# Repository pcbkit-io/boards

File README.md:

# PCBKit boards

Circuit boards as plain KiCad projects, each one you can open in [PCBKit](https://pcbkit.io),
run as the device it is, and order. The KiCad files are the design; a board with a processor carries its program beside it
(`firmware/`, or the folder its `.pcbkit/device.yaml` names) and PCBKit builds it and runs the
image on its models of the board's chips, wired as the board's copper wires them: the same image
you flash onto the ordered board.

What a board cannot say itself is in its `.pcbkit/device.yaml`: the program's folder where it is
not `firmware`, files the program is built with and the repository does not hold (the Doom
boards' `DOOM1.WAD`, by address and SHA-256), a bare panel's size, the keys that work its
buttons. `pcbkit device plan` in a board's folder says what was recognised and how it is wired;
`pcbkit device build` and `pcbkit device run --seconds 5` build and run it.

| Folder | What is in it |
|---|---|
| [`devices/`](devices) | Real devices end to end: an STM32G431 sensor node on a robot's CAN bus and a 24 V AC thermostat on an ESP32, each with the world around it simulated |
| [`lab/`](lab) | Interactive boards: an ATmega328P (or two) running real C firmware against sensors, buttons, knobs, displays and servos you can change while it runs |
| [`arduino/`](arduino) | Arduino projects to play with: an Arduino Nano running a sketch with the usual libraries (Adafruit SSD1306 and SHT31, Sensirion SCD4x, LiquidCrystal, Servo): a weather station, a CO₂ monitor, a thermostat, a character-LCD runner, a pocket console with six games, Simon, a drawing screen |
| [`examples/`](examples) | Boards to learn from: a design PCBKit placed and routed from parts and connections, circuit blocks, open boards by their authors |
| [`assets/`](assets) | Files the simulation needs besides the boards: the boot ROMs of Espressif chips (Apache 2.0, from Espressif) |
| [`doom/`](doom) | Doom handhelds: eleven boards from a 10-cent CH32V003 to a Teensy 4.1 (RP2040, RP2350, ESP32-C3, ESP32-S3, STM32F411, i.MX RT1062), each ordered at JLCPCB as it is, flashed over USB and playing Doom from two 18650 cells |

Each folder is a family of boards with its own README; each board's folder is one project with
its README (what it is, how to order, flash and charge it, its parts and check results).

## The registry

[`registry.json`](registry.json) is the catalogue of these boards: their categories and, for each
board, its title, summary, tags, chips, licence, author, origin, folder, how it opens and whether
it is ready to order (`production`), as the schema [`registry.schema.json`](registry.schema.json)
says. PCBKit's app, its board library and pcbkit.io read nothing else: `node scripts/publish.mjs`
checks every board with the pcbkit command-line tool and publishes the registry and each board's
files to https://library.pcbkit.io/demos/ (the app reads it there without being rebuilt); a
board's picture is PCBKit's, drawn from its folder at the published commit
(`https://app.pcbkit.io/embed/github/pcbkit-io/boards/tree/<commit>/<path>.webp`). A new board: its
folder and an entry, then publish.

**Every interactive board is a real board**: it runs in the app, and it can be ordered from a
fab as it is and flashed after assembly (a USB bootloader or a programming header), so the image
that runs in the app runs on the board.

## Checking a board

`pcbkit check` in a board's folder runs KiCad's own electrical and design rule checks on it and
says what they found (the command comes with [PCBKit's plugin](https://github.com/pcbkit-io/agent-plugin)).

## Licences

Each family has its own: `devices/`, `lab/`, `arduino/` and `examples/` are CC0 1.0 (public domain), but for the open
boards by other authors, which keep theirs (`LICENSE.md` in their folders); `doom/` is the GNU GPL
v2 ([`doom/LICENSE`](doom/LICENSE)), the licence of the Doom engines it carries.

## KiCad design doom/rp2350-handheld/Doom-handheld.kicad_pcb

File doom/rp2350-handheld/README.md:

# RP2350 Doom handheld

A carrier board for a **Pimoroni Pico Plus 2** (RP2350B with 16 MB of flash and 8 MB of PSRAM)
under a **2.8" ILI9341 SPI TFT module** (the MSP2807, with touch), with a d-pad, strafe, fire, use,
menu and enter buttons. Power and flashing go through the Pico's USB-C. The outline is a red
keycard with a lanyard slot; the wordmark on the silkscreen is our own drawing.

## Run it in the browser

Open https://app.pcbkit.io/github/pcbkit-io/boards/tree/main/doom/rp2350-handheld, open
the Laboratory and press **Run**: the page builds `doom/` for the RP2350 (with `DOOM1.WAD` linked
into flash), boots the image on a register-level model of the chip and its PSRAM, and draws the
ILI9341's frames on the board. Play with the keyboard (arrows, F fire, Space use, comma/period
strafe, M menu, Enter) or a gamepad (`input.js` maps a standard controller).

## Parts

| Ref | Part | Note |
|---|---|---|
| U1 | Pimoroni Pico Plus 2 (PIM722) | on the back, on two 1x20 headers |
| lcd | 2.8" ILI9341 SPI TFT with touch (MSP2807) | on a 1x14 female header; the touch shares SPI0 and stays deselected |
| up, down, left, right, strafeLeft, strafeRight, fire, use, menu, enter | 6 x 6 mm tactile switch | to ground; the RP2350's pull-ups |
| J1 | 1x3 2.54 mm header | the console: UART0 at 115200 baud (TX, RX, GND) |
| BT1, BT2, F1, F2 | two Keystone 1042 18650 holders on the back; 2 A resettable fuses (Littelfuse 1812L200/16GR) | the cells in parallel, each through its own fuse (a cell put in backwards trips them instead of shorting the other), then the reverse-cell P-FET and DW01A + FS8205A protection |

## Pins

| Signal | GPIO |
|---|---|
| Display SCK, MOSI (SPI0) | GP18, GP19 |
| Display CS, D/C, RESET, backlight | GP17, GP20, GP21, GP22 |
| Up, down, left, right, fire, use, strafe left, strafe right, menu, enter | GP2 … GP11 |
| Console TX, RX (UART0) | GP0, GP1 |
| PSRAM chip select | GP47 (on the Pico Plus 2) |

## The firmware

`doom/doom_rp2350.c` is the platform layer: clocks (12 MHz crystal, 150 MHz from the PLL), the
PSRAM on the QSPI interface, the display over SPI0 at 25 MHz, the buttons, the timer. The engine
in `doom/` is sysprog21/doom_riscv, unchanged. The program runs on the RP2350's RISC-V (Hazard3)
cores from flash; the zone heap and the screens are in PSRAM. There is no sound.

The simulation runs one instruction per clock and does not charge flash or PSRAM latency, so the
board itself may draw fewer frames per second than the browser shows.

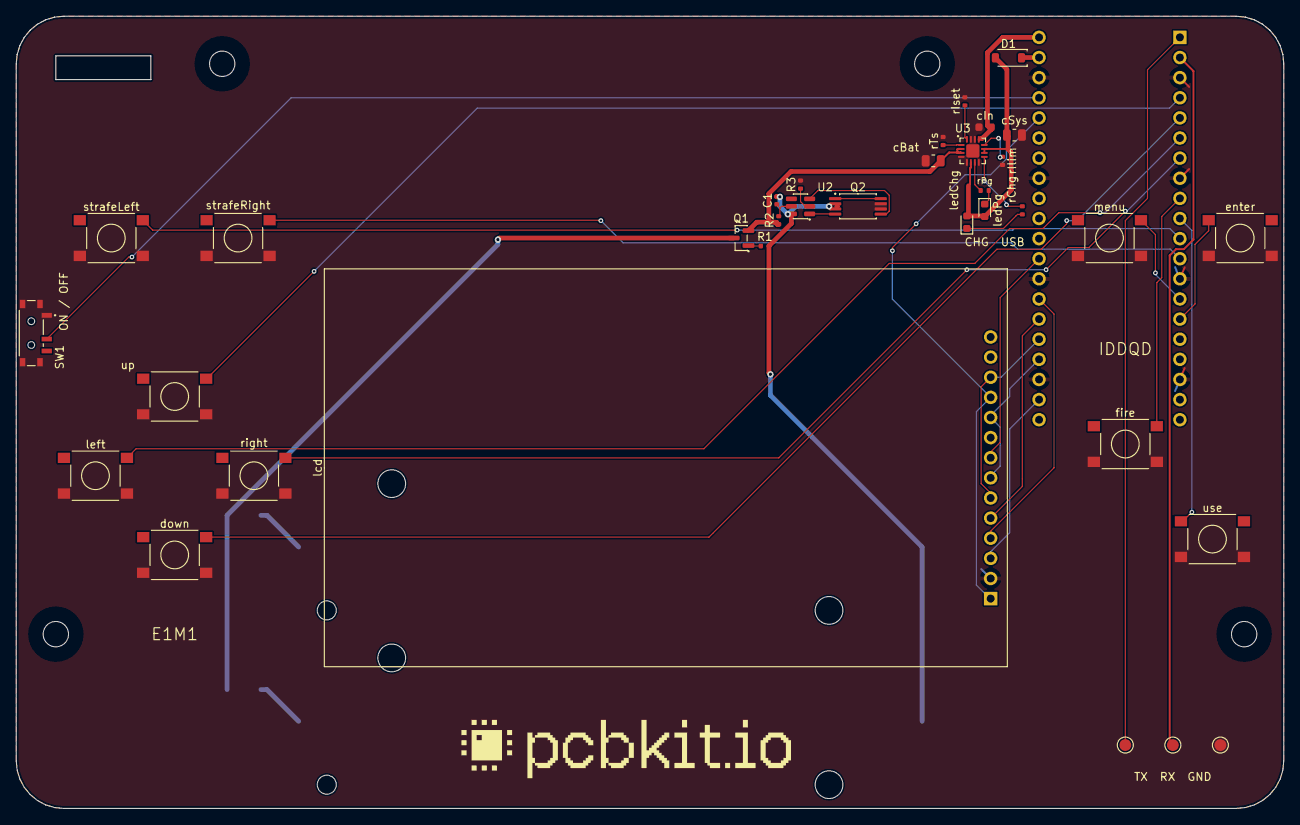
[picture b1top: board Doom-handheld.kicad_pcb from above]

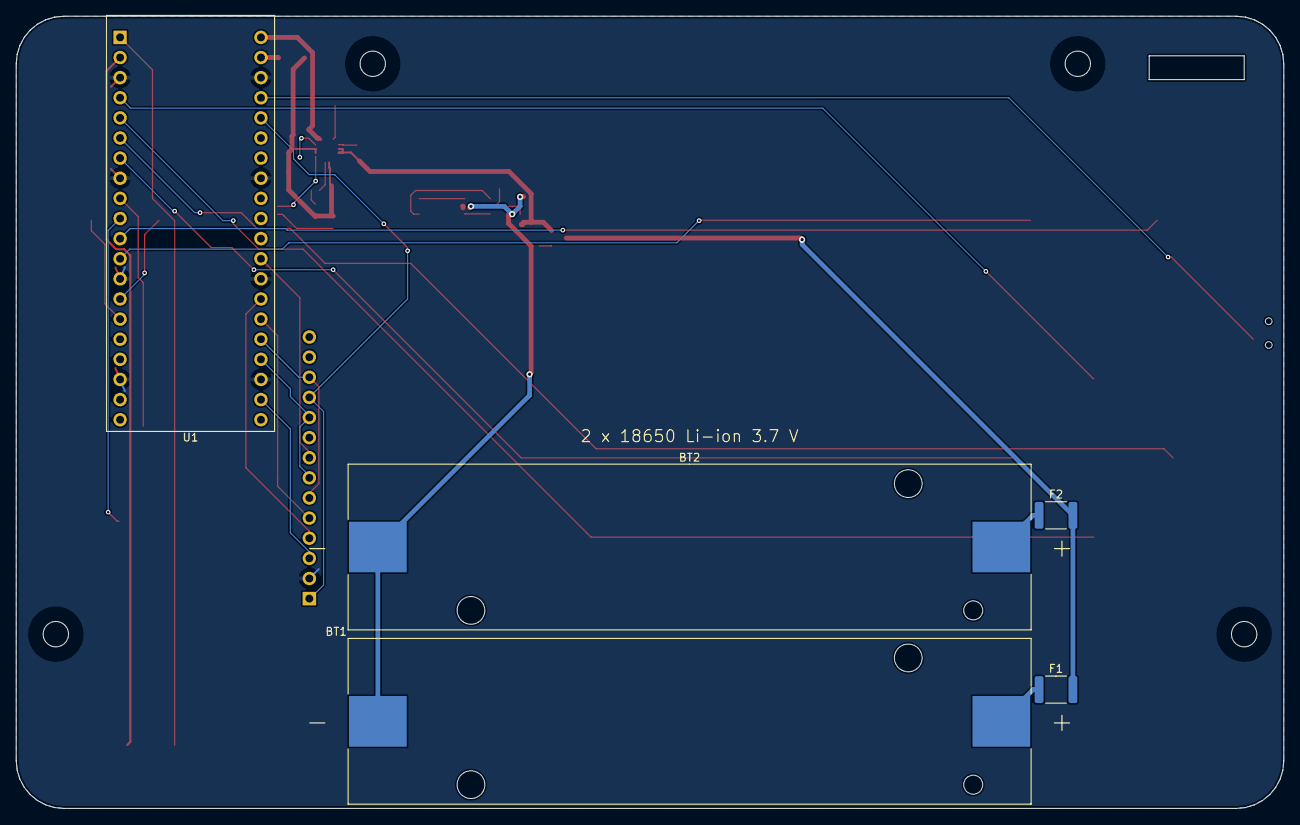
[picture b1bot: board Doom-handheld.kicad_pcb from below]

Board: 2 copper layers, 160.0 x 100.0 mm, 44 parts (5 on the bottom side), 42 nets.

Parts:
BT1, BT2: 1042; BatteryHolder_Keystone_1042_1x18650
C1: 100nF; C_0402_1005Metric
D1: 1N5819HW-7-F; D_SOD-123
F1, F2: PTC 2000mA; Fuse_1812_4532Metric
H1, H2, H3, H4: MountingHole_3.2mm_M3
Q1: AO3401A; SOT-23
Q2: FS8205A; TSSOP-8_4.4x2.93mm_P0.65mm
R1: 100kohm; R_0402_1005Metric
R2: 100ohm; R_0402_1005Metric
R3: 1kohm; R_0402_1005Metric
SW1: MSK12C02; SW_Slide_SPDT_Shouhan_MSK12C02
U1: PIM724; Pimoroni_Pico_Plus_2_Socket_2x20_P2.54mm_W17.78mm
U2: DW01A; SOT-6_1.6x2.9mm_P0.95mm
U3: BQ24075RGTR; QFN-16-1EP_3x3mm_P0.5mm_EP1.68x1.68mm
cBat: 4.7uF; C_0805_2012Metric
cIn: 1uF; C_0603_1608Metric
cSys: 4.7uF; C_0805_2012Metric
down: PTS645SM43SMTR92 LFS; SW_Tactile_SPST_6x6mm_SMD
enter: PTS645SM43SMTR92 LFS; SW_Tactile_SPST_6x6mm_SMD
fire: PTS645SM43SMTR92 LFS; SW_Tactile_SPST_6x6mm_SMD
lcd: MSP2807 2.8in 240x320 SPI TFT module with touch (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; TFT_2.8in_ILI9341_Socket_1x14_P2.54mm
ledChg: red; LED_0603_1608Metric
ledPg: green; LED_0603_1608Metric
left: PTS645SM43SMTR92 LFS; SW_Tactile_SPST_6x6mm_SMD
logo: Logo_PCBKit_pcbkit.io
menu: PTS645SM43SMTR92 LFS; SW_Tactile_SPST_6x6mm_SMD
rChg: 1.5kohm; R_0402_1005Metric
rIlim: 1.18kohm; R_0402_1005Metric
rIset: 1.13kohm; R_0402_1005Metric
rPg: 1.5kohm; R_0402_1005Metric
rTs: 10kohm; R_0402_1005Metric
right: PTS645SM43SMTR92 LFS; SW_Tactile_SPST_6x6mm_SMD
strafeLeft: PTS645SM43SMTR92 LFS; SW_Tactile_SPST_6x6mm_SMD
strafeRight: PTS645SM43SMTR92 LFS; SW_Tactile_SPST_6x6mm_SMD
tpGnd: TestPoint_Round_D1.5mm
tpRx: TestPoint_Round_D1.5mm
tpTx: TestPoint_Round_D1.5mm
up: PTS645SM43SMTR92 LFS; SW_Tactile_SPST_6x6mm_SMD
use: PTS645SM43SMTR92 LFS; SW_Tactile_SPST_6x6mm_SMD

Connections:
BAT: Q1.2 (S), R2.1 (a), U3.2 (BAT), U3.3 (BAT), cBat.1 (a)
BAT_IN: F1.2 (b), F2.2 (b), Q1.3 (D)
CELL1_P: BT1.2 (C2), F1.1 (a)
CELL2_P: BT2.2 (C2), F2.1 (a)
CELL_N: BT1.1 (C1), BT2.1 (C1), C1.2 (b), Q2.2 (S1), Q2.3 (S1), R1.2 (b), U2.6 (GND)
CHG_LED: ledChg.1 (K), rChg.1 (a)
CHG_N: U3.9 (nCHG), rChg.2 (b)
DOWN: U1.5 (GP3), down.1 (a)
ENTER: U1.15 (GP11), enter.1 (a)
FIRE: U1.9 (GP6), fire.1 (a)
GND: Q2.6 (S2), Q2.7 (S2), R3.2 (b), SW1.1 (A), SW1.4 (SHELL), U1.3 (GND), U1.8 (GND), U1.13 (GND), U1.18 (GND), U1.23 (GND), U1.28 (GND), U1.33 (AGND), U1.38 (GND), U3.4 (nCE), U3.5 (EN2), U3.8 (VSS), U3.14 (TMR), U3.15 (SYSOFF), U3.17 (VSS), cBat.2 (b), cIn.2 (b), cSys.2 (b), down.2 (b), enter.2 (b), fire.2 (b), lcd.2 (GND), left.2 (b), menu.2 (b), rIlim.2 (b), rIset.2 (b), rTs.2 (b), right.2 (b), strafeLeft.2 (b), strafeRight.2 (b), tpGnd.1, up.2 (b), use.2 (b)
ILIM: U3.12 (ILIM), rIlim.1 (a)
ISET: U3.16 (ISET), rIset.1 (a)
LCD_CS: U1.22 (GP17), lcd.3 (CS)
LCD_DC: U1.26 (GP20), lcd.5 (DC)
LCD_LED: U1.29 (GP22), lcd.8 (LED)
LCD_MOSI: U1.25 (GP19), lcd.6 (SDI), lcd.12 (T_DIN)
LCD_RESET: U1.27 (GP21), lcd.4 (RESET)
LCD_SCK: U1.24 (GP18), lcd.7 (SCK), lcd.10 (T_CLK)
LEFT: U1.6 (GP4), left.1 (a)
MENU: U1.14 (GP10), menu.1 (a)
unnamed: C1.1 (a), R2.2 (b), U2.5 (VCC)
unnamed: Q2.4 (G1), U2.1 (OD)
unnamed: Q2.5 (G2), U2.3 (OC)
unnamed: R3.1 (a), U2.2 (CS)
PG_LED: ledPg.1 (K), rPg.2 (b)
PG_N: U3.7 (nPGOOD), rPg.1 (a)
PWR_EN: SW1.2 (COM), U1.37 (P3V3_EN)
RIGHT: U1.7 (GP5), right.1 (a)
RX: U1.2 (GP1), tpRx.1
STRAFE_L: U1.11 (GP8), strafeLeft.1 (a)
STRAFE_R: U1.12 (GP9), strafeRight.1 (a)
SYS: D1.2 (A), U3.6 (EN1), U3.10 (OUT), U3.11 (OUT), cSys.1 (a), ledChg.2 (A), ledPg.2 (A)
TS: U3.1 (TS), rTs.1 (a)
TX: U1.1 (GP0), tpTx.1
U2Support/DRAIN: Q2.1 (D12), Q2.8 (D12)
UP: U1.4 (GP2), up.1 (a)
USE: U1.10 (GP7), use.1 (a)
V3: U1.36 (P3V3), lcd.1 (VCC), lcd.11 (T_CS)
VBUS: U1.40 (VBUS), U3.13 (IN), cIn.1 (a)
VSYS: D1.1 (K), U1.39 (VSYS)
reversed/gate: Q1.1 (G), R1.1 (a)

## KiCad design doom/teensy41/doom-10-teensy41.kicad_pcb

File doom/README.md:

# Doom handhelds

Circuit boards that run Doom, designed in [PCBKit](https://pcbkit.io). Every board is a PCBKit
project (a KiCad project with its `.pcbkit/` design): open one in the app, press **Run**, and the
same firmware that would be flashed onto the ordered board is built in your browser and plays
there on a simulation of its chips; order the board, flash the image, and it plays on the desk.

Open them at **https://app.pcbkit.io/github/pcbkit-io/boards/tree/main/doom**.

| Board | What it is |
|---|---|
| [`rp2350-handheld`](rp2350-handheld) | Pimoroni Pico Plus 2 (RP2350B, 16 MB flash, 8 MB PSRAM) under a 2.8" ILI9341 screen, ten buttons, USB-C power; a red keycard with a lanyard slot |

Ten more designs explore the range, from the cheapest chip that can run Doom at all to a
Cortex-M7 at 600 MHz: different processors, screens, memories and sound, one power design. Each
is routed, passes `check` and is ready to order, and each has its program in `doom/`: opened from
its GitHub link in PCBKit, it builds in the page and plays in the simulation, and its README says
how to flash it over USB on arrival.

| Board | Processor | Screen | Flashing on arrival |
|---|---|---|---|
| [`v003-emu`](v003-emu) | CH32V003 (RISC-V, 2 KB RAM) emulating a larger RISC-V, game in 8 MB SPI PSRAM | Nokia 5110 | WCH-LinkE on the SWIO header |
| [`pico-oled`](pico-oled) | Raspberry Pi Pico (RP2040) on sockets | 2.42" mono OLED | the Pico's USB: BOOTSEL, UF2 |
| [`c3-pocket`](c3-pocket) | ESP32-C3 module (RISC-V) | 1.3" colour TFT | USB-C: the C3's USB Serial/JTAG (esptool) |
| [`rp2040-tft`](rp2040-tft) | bare RP2040, 16 MB flash, microSD, PWM sound | 1.8" colour TFT | USB-C: BOOT + RESET, UF2; SWD header |
| [`f411-psram`](f411-psram) | STM32F411 (Cortex-M4F) with 8 MB SPI PSRAM and flash, I2S amplifier | 2.0" TFT | USB-C: the ROM's DFU (BOOT + RESET); SWD header |
| [`pico2-carrier`](pico2-carrier) | Pimoroni Pico Plus 2 carrier with a headphone DAC | 2.8" ILI9341 touch | the module's USB: BOOTSEL, UF2 |
| [`rp2350-psram`](rp2350-psram) | bare RP2350A with QSPI flash and 8 MB PSRAM, microSD, I2S amplifier, fuel gauge | 2.0" TFT | USB-C: BOOT + RESET, UF2; SWD header |
| [`s3-handheld`](s3-handheld) | ESP32-S3 module (Xtensa, 8 MB PSRAM), microSD, I2S amplifier, fuel gauge | 2.8" touch TFT | USB-C: the S3's USB Serial/JTAG (esptool) |
| [`s3-rgb`](s3-rgb) | ESP32-S3 driving a raw 480×272 RGB panel, buttons on an I2C expander, stereo DAC | 4.3" RGB | USB-C: the S3's USB Serial/JTAG (esptool) |
| [`teensy41`](teensy41) | Teensy 4.1 (Cortex-M7, 600 MHz), DAC with jack and speaker, fuel gauge | 3.5" touch TFT | the Teensy's USB: Teensy Loader |

Every board runs from **two 18650 Li-ion cells in parallel** (1S2P, Keystone 1042 holders on the
back) behind a reverse-cell P-MOSFET and DW01A + FS8205A protection, charged over USB by a BQ24075
with power path (the board runs from USB while it charges), as [`rp2350-handheld`](rp2350-handheld)
does. Every assembled part has an LCSC code for JLCPCB's assembly; modules and screens plug into
sockets it solders. Each board's README says how to charge it, how to flash it, what to plug in
by hand and its parts, with its `check` and readiness results.

## Licences

- The game engine in each board's `doom/` is id Software's Linux Doom source as released under the
  GNU GPL v2: [sysprog21/doom_riscv](https://github.com/sysprog21/doom_riscv) at `81ccabe`
  unchanged on most boards; [kilograham/rp2040-doom](https://github.com/kilograham/rp2040-doom) at
  `29a453c` (GPL v2, its compressed level format) on `pico-oled`, `rp2040-tft` and `c3-pocket`, with
  the changes PCBKit's kits need marked `PCBKIT`.
- Everything else here (the boards, their designs and KiCad files, the platform layers
  `doom/doom_*.c`, the simulations' scripts) is by PCBKit, under the same licence: the GNU
  General Public License v2 ([`LICENSE`](LICENSE)).
- The game's data is not in this repository. Each design declares the shareware `DOOM1.WAD` (or
  rp2040-doom's compressed `DOOM1.WHX`; id Software, free to share unmodified) by where it is
  published and its SHA-256; the build downloads it, checks it and links it into the firmware.

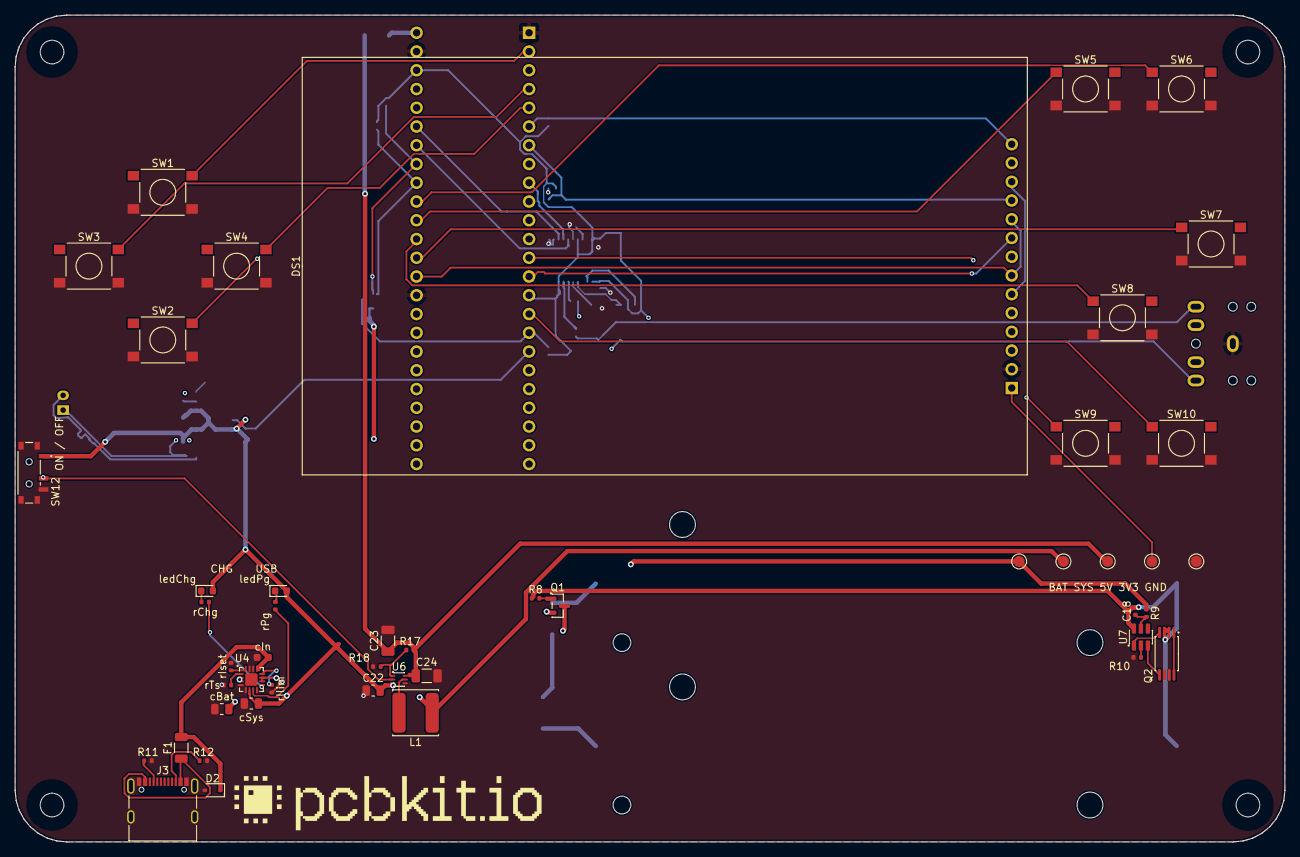
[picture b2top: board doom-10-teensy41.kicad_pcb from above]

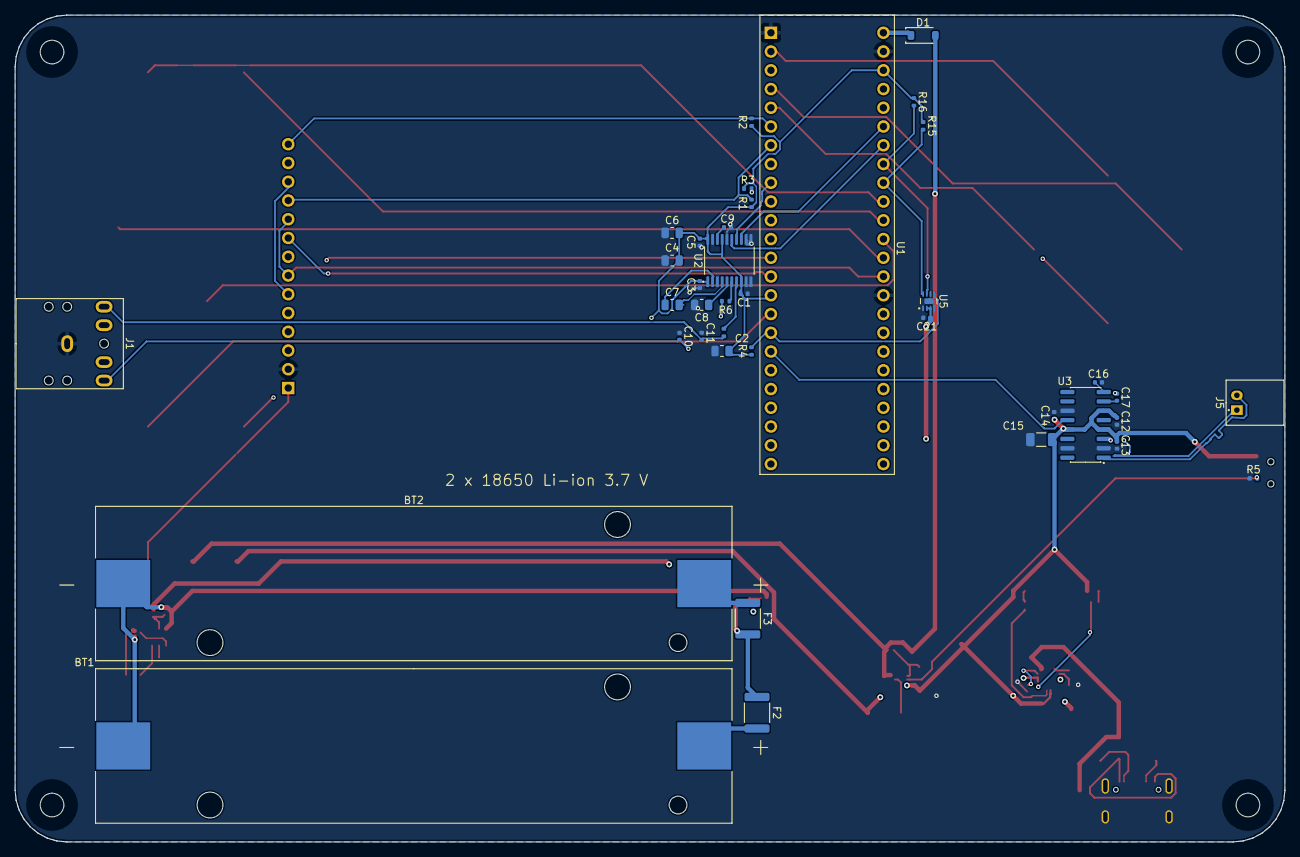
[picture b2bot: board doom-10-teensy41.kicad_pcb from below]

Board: 4 copper layers, 172.0 x 112.0 mm, 90 parts (38 on the bottom side), 68 nets.

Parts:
BT1, BT2: 1042; BatteryHolder_Keystone_1042_1x18650
C1, C3, C5, C9, C18, C21: 100nF; C_0402_1005Metric
C2, C4, C6, C22: 10uF; C_0805_2012Metric
C7, C8: 2.2uF; C_0805_2012Metric
C10, C11: 2.2nF; C_0402_1005Metric
C12, C13, C14, C16: 1uF; C_0402_1005Metric
C15, C23, C24: 22uF; C_1206_3216Metric
C17: 470nF; C_0402_1005Metric
D1: 1N5819HW-7-F; D_SOD-123
D2: tvs 5V; D_SOD-323
DS1: MSP3520 3.5in 320x480 SPI TFT module with touch (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; TFT_3.5in_ILI9488_Socket_1x14_P2.54mm
F1: PTC 1100mA; Fuse_1206_3216Metric
F2, F3: PTC 2000mA; Fuse_1812_4532Metric
H1, H2, H3, H4: MountingHole_3.2mm_M3
J1: SJ1-3525N; Jack_3.5mm_SameSky_SJ1-352XN_Horizontal
J3: USB4105-GF-A; USB_C_Receptacle_USB2.0_16P
J5: S2B-PH-K-S(LF)(SN); JST_PH_S2B-PH-K_1x02_P2.00mm_Horizontal
L1: 1uH; L_Power_6x6mm
Q1: AO3401A; SOT-23
Q2: FS8205A; TSSOP-8_4.4x2.93mm_P0.65mm
R1, R2, R3, R4: 10kohm; R_0402_1005Metric
R5: 1Mohm; R_0402_1005Metric
R6, R7: 470ohm; R_0402_1005Metric
R8, R18: 100kohm; R_0402_1005Metric
R9: 100ohm; R_0402_1005Metric
R10: 1kohm; R_0402_1005Metric
R11, R12: 5.1kohm; R_0402_1005Metric
R15, R16: 3.3kohm; R_0402_1005Metric
R17: 732kohm; R_0402_1005Metric
SW1, SW2, SW3, SW4, SW5, SW6, SW7, SW8, SW9, SW10: PTS645SM43SMTR92 LFS; SW_Tactile_SPST_6x6mm_SMD
SW12: MSK12C02; SW_Slide_SPDT_Shouhan_MSK12C02
U1: TEENSY41; Teensy41_Socket_2x24_P2.54mm_W15.24mm
U2: PCM5102APWR; TSSOP-20_4.4x6.5mm_P0.65mm
U3: PAM8403DR; SOIC-16_3.9x9.9mm_P1.27mm
U4: BQ24075RGTR; QFN-16-1EP_3x3mm_P0.5mm_EP1.68x1.68mm
U5: MAX17048G+T10; DFN-8-1EP_2x2mm_P0.5mm_EP0.8x1.2mm
U6: TPS61023DRLR; SOT-563
U7: DW01A; SOT-6_1.6x2.9mm_P0.95mm
cBat: 4.7uF; C_0805_2012Metric
cIn: 1uF; C_0603_1608Metric
cSys: 4.7uF; C_0805_2012Metric
ledChg: red; LED_0603_1608Metric
ledPg: green; LED_0603_1608Metric
logo: Logo_PCBKit_pcbkit.io
rChg: 1.5kohm; R_0402_1005Metric
rIlim: 1.18kohm; R_0402_1005Metric
rIset: 1.13kohm; R_0402_1005Metric
rPg: 1.5kohm; R_0402_1005Metric
rTs: 10kohm; R_0402_1005Metric
tpBat: TestPoint_Round_D1.5mm
tpGnd: TestPoint_Round_D1.5mm
tpSys: TestPoint_Round_D1.5mm
tpV3, tpV5: TestPoint_Round_D1.5mm

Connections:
AMP_SD: U1.18 (D26), U3.12 (SHDN)
BAT: C21.1 (a), Q1.2 (S), R9.1 (a), U4.2 (BAT), U4.3 (BAT), U5.2 (CELL), U5.3 (VDD), cBat.1 (a), tpBat.1
BAT_IN: F2.2 (b), F3.2 (b), Q1.3 (D)
BOOST_EN: R5.1 (a), SW12.2 (COM), U6.2 (EN)
CELL1_P: BT1.2 (C2), F2.1 (a)
CELL2_P: BT2.2 (C2), F3.1 (a)
CELL_N: BT1.1 (C1), BT2.1 (C1), C18.2 (b), Q2.2 (S1), Q2.3 (S1), R8.2 (b), U7.6 (GND)
CHG_LED: ledChg.1 (K), rChg.2 (b)
CHG_N: U4.9 (nCHG), rChg.1 (a)
DAC_LDO: C9.1 (a), U2.18 (LDOO)
DAC_VNEG: C8.1 (a), U2.5 (VNEG)
DOWN: SW2.1 (a), U1.3 (D1)
ENTER: SW10.1 (a), U1.16 (D24)
FIRE: SW7.1 (a), U1.37 (D14)
FUEL_ALRT: R4.2 (b), U1.17 (D25), U5.5 (ALRT)
GND: C1.2 (b), C2.2 (b), C3.2 (b), C4.2 (b), C5.2 (b), C6.2 (b), C8.2 (b), C9.2 (b), C10.2 (b), C11.2 (b), C12.2 (b), C13.2 (b), C14.2 (b), C15.2 (b), C16.2 (b), C21.2 (b), C22.2 (b), C23.2 (b), C24.2 (b), D2.2 (A), DS1.2 (GND), J1.1 (SLEEVE), J3.A1 (GND), J3.A12, J3.B1 (GND), J3.B12, J3.S1 (SHIELD), Q2.6 (S2), Q2.7 (S2), R5.2 (b), R10.2 (b), R11.2 (b), R12.2 (b), R18.2 (b), SW1.2 (b), SW2.2 (b), SW3.2 (b), SW4.2 (b), SW5.2 (b), SW6.2 (b), SW7.2 (b), SW8.2 (b), SW9.2 (b), SW10.2 (b), SW12.3 (B), SW12.4 (SHELL), U1.1 (GND), U1.26 (GND), U1.39 (GND), U2.3 (CPGND), U2.9 (AGND), U2.10 (DEMP), U2.11 (FLT), U2.12 (SCK), U2.16 (FMT), U2.19 (DGND), U3.2 (PGND), U3.11 (GND), U3.15 (PGND), U4.4 (nCE), U4.5 (EN2), U4.8 (VSS), U4.14 (TMR), U4.15 (SYSOFF), U4.17 (VSS), U5.1 (CTG), U5.4 (GND), U5.6 (QSTRT), U5.9 (EP), U6.4 (GND), cBat.2 (b), cIn.2 (b), cSys.2 (b), rIlim.2 (b), rIset.2 (b), rTs.2 (b), tpGnd.1
I2S_BCK: U1.30 (D21), U2.13 (BCK)
I2S_DIN: U1.9 (D7), U2.14 (DIN)
I2S_LRCK: U1.31 (D20), U2.15 (LRCK)
ILIM: U4.12 (ILIM), rIlim.1 (a)
ISET: U4.16 (ISET), rIset.1 (a)
LCD_BL: DS1.8 (LED), U1.8 (D6)
LCD_CS: DS1.3 (CS), R3.2 (b), U1.12 (D10)
LCD_DC: DS1.5 (DC), U1.11 (D9)
LCD_RST: DS1.4 (RESET), U1.10 (D8)
LEFT: SW3.1 (a), U1.4 (D2)
LINE_L: C10.1 (a), C17.1 (a), J1.2 (TIP), R6.2 (b)
LINE_R: C11.1 (a), J1.3 (RING), R7.1 (a)
MENU: SW9.1 (a), U1.29 (D22)
MISO: DS1.9 (SDO), DS1.13 (T_DO), U1.14 (D12)
MOSI: DS1.6 (SDI), DS1.12 (T_DIN), U1.13 (D11)
unnamed: C7.2 (b), U2.2 (CAPP)
unnamed: C7.1 (a), U2.4 (CAPM)
unnamed: C16.1 (a), U3.8 (VREF)
unnamed: C17.2 (b), U3.7 (INL)
unnamed: C18.1 (a), R9.2 (b), U7.5 (VCC)
unnamed: L1.2 (b), U6.5 (SW)
unnamed: Q2.4 (G1), U7.1 (OD)
unnamed: Q2.5 (G2), U7.3 (OC)
unnamed: R6.1 (a), U2.6 (OUTL)
unnamed: R7.2 (b), U2.7 (OUTR)
unnamed: R10.1 (a), U7.2 (CS)
unnamed: R17.1 (a), R18.1 (a), U6.1 (FB)
PG_LED: ledPg.1 (K), rPg.1 (a)
PG_N: U4.7 (nPGOOD), rPg.2 (b)
RIGHT: SW4.1 (a), U1.5 (D3)
SCK: DS1.7 (SCK), DS1.10 (T_CLK), U1.38 (D13)
SCL: R16.2 (b), U1.32 (D19), U5.7 (SCL)
SDA: R15.1 (a), U1.33 (D18), U5.8 (SDA)
SPK_N: J5.1 (C1), U3.3 (OUTLN)
SPK_P: J5.2 (C2), U3.1 (OUTLP)
STRAFE_L: SW5.1 (a), U1.35 (D16)
STRAFE_R: SW6.1 (a), U1.34 (D17)
SYS: C12.1 (a), C13.1 (a), C14.1 (a), C15.1 (a), C22.1 (a), L1.1 (a), SW12.1 (A), U3.4 (PVDD), U3.6 (VDD), U3.13 (PVDD), U4.6 (EN1), U4.10 (OUT), U4.11 (OUT), U6.3 (VIN), cSys.1 (a), ledChg.2 (A), ledPg.2 (A), tpSys.1
TS: U4.1 (TS), rTs.1 (a)
T_CS: DS1.11 (T_CS), R1.2 (b), U1.7 (D5)
T_IRQ: DS1.14 (T_IRQ), R2.2 (b), U1.6 (D4)
U7Support/DRAIN: Q2.1 (D12), Q2.8 (D12)
UP: SW1.1 (a), U1.2 (D0)
USE: SW8.1 (a), U1.36 (D15)
V3: C1.1 (a), C2.1 (a), C3.1 (a), C4.1 (a), C5.1 (a), C6.1 (a), DS1.1 (VCC), R1.1 (a), R2.1 (a), R3.1 (a), R4.1 (a), R15.2 (b), R16.1 (a), U1.15 (P3V3), U1.27 (P3V3), U2.1 (CPVDD), U2.8 (AVDD), U2.17 (XSMT), U2.20 (DVDD), tpV3.1
V5: C23.1 (a), C24.1 (a), D1.2 (A), R17.2 (b), U6.6 (VOUT), tpV5.1
VBUS: D2.1 (K), F1.2 (b), U4.13 (IN), cIn.1 (a)
VIN: D1.1 (K), U1.25 (VIN)
reversed/gate: Q1.1 (G), R8.1 (a)
usb/cc1: J3.A5 (CC1), R11.1 (a)
usb/cc2: J3.B5 (CC2), R12.1 (a)
usb/vbusIn: F1.1 (a), J3.A4 (VBUS), J3.A9, J3.B4 (VBUS), J3.B9

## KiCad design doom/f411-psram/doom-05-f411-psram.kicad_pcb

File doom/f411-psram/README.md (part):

# 05 · f411-psram — an STM32 "Black Pill" chip with 8 MB of SPI PSRAM

The STM32F411CEU6 (the chip of WeAct's Black Pill) is a fast Cortex-M4F with only 128 KB of SRAM and
no memory-mapped QSPI, so the board adds an 8 MB APS6404L PSRAM and a 16 MB W25Q128 on SPI1 and the
port pages Doom's heap through a software cache. A 2.0" IPS, an I2S amplifier, eight buttons, and two
18650 cells it charges from its USB-C. Firmware goes in through the same USB-C by the ROM's USB DFU
bootloader, or SWD. JLCPCB assembles everything but the display module, which plugs into the socket
it solders.

| | |
|---|---|
| Processor | STM32F411CEU6 (UFQFPN-48): Arm **Cortex-M4F** (ARMv7E-M, Thumb-2, DSP, single-precision FPU), 100 MHz, 128 KB SRAM, 512 KB flash with ART accelerator; 25 MHz HSE crystal |
| Memory | APS6404L-3SQR 8 MB PSRAM (CS PA4) and W25Q128JV 16 MB flash (CS PB2) on SPI1 at 50 MHz (PA5 SCK, PA6 MISO, PA7 MOSI) |
| Display | 2.0" 240 × 320 IPS, ST7789 (MSP2008), SPI2 at 25 MHz (PB13 SCK, PB15 MOSI, PB12 CS, PB14 DC, PB1 RES), backlight PWM on PB10 (TIM2_CH3); used landscape 320 × 240 |
| Input | 8 × 6 mm tact switches: up PA1, down PA2, left PA3, right PB4, fire PB6, use PB7, strafe PB8, menu PB0 (internal pull-ups) |
| Sound | I2S3 (PB3 CK, PA15 WS, PB5 SD) → MAX98357A (mono mix, 9 dB) → 8 Ω speaker |
| Power | 2 × 18650 Li-ion in parallel (1S2P, a 2 A resettable fuse per cell) in Keystone 1042 holders → reverse-cell P-FET (AO3401A) → DW01A + FS8205A; BQ24075 charger with power path from USB-C; SYS → TLV75533 LDO (3.3 V, switched by its EN) and the amplifier |
| Programming | USB-C to PA11/PA12: hold BOOT (BOOT0 → 3.3 V) and press RESET → ROM DFU (`dfu-util`); SWD header J1 on the back (VCC, SWDIO, SWCLK, NRST, GND) for an ST-LINK |
| Board | 140 × 104 mm, **4 layers**, four M3 holes; front: display, buttons, BOOT, RESET, on/off switch, USB-C (top edge), charger, speaker connector (right edge), test pads; back: MCU, memories, amplifier, regulator, SWD header, the two cells |

<!-- STATUS -->
**Board status** (measured on the dev host with PCBKit's CLI): `pcbkit check`: complete — 0 errors, 3 warnings (erc-rail-name), 0 unrouted nets. 81 components, 62 nets, 759 track segments (2408 mm), 86 vias.
`analysis.run { lens: "ready" }`: Typical scenario, partly by family estimates. Nothing to fix, 2 to consider, 17 ok: weigh the warnings (tell the person about the ones that are their choice), then the board is ready to order.
`pcbkit export --format fab` succeeds without `--force`: every assembled line of the BOM has an LCSC code.
<!-- /STATUS -->

Warnings left, and why they are acceptable:

| Warning | Why |
|---|---|
| `diff-pair-uncoupled`, `skew` on DP / DN | USB full speed (12 Mbit/s, used only by the ROM's DFU): the connector is on the front's top edge, the processor on the back; tens of mm uncoupled and a few mm of skew are harmless at this rate |
| J1 is not on an edge | the SWD header, for a programmer's clip during development: not a cable that stays |
| heat sources need exact thermal parameters; chips estimated by their family | the thermal estimate's own caveat: nothing on this board dissipates more than a few hundred mW |

## Run it in the browser

Open https://app.pcbkit.io/github/pcbkit-io/boards/tree/main/doom/f411-psram, open the
Laboratory and press **Build & run**: the page builds both programs — `emu/` for the STM32F411
(Cortex-M4F) and `doom/` for the computer it emulates (pcbkit-virt, with `DOOM1.WAD` linked in) —
puts the second in the W25Q128 and runs the board.

## How Doom fits

The F411 has 128 KB of SRAM and no memory-mapped QSPI, so its firmware (`emu/`, 19.5 KB) is a
RISC-V computer built from the serial chips, as on doom-01: an RV32IMAC interpreter
(`emu/rvemu.c`) with a 64 KB direct-mapped write-back cache (2048 lines of 32 bytes) in its SRAM
over the APS6404L (the guest's 8 MB of RAM) and the W25Q128 (the guest, `doom/`: Doom for
pcbkit-virt with the WAD linked in, its code and constants read where they lie). A miss is one
SPI transaction at 50 MHz with fast read (0Bh): 5.9 µs with the chip selected, inside the
PSRAM's 8 µs limit. Each guest frame (320 × 200, 8-bit) goes to the ST7789 through the guest's
colour table as RGB565, on SPI2 at 25 MHz. Measured in PCBKit's simulator: the title screen at
about 40 s of device time, in full colour; then the demo, a few frames a second.

## Power

Two 18650 Li-ion cells in Keystone 1042 holders on the back, in parallel (1S2P, 3.0–4.2 V). From the
cells to the board:

- **Reverse cells:** an AO3401A P-MOSFET in the plus line, its gate at the cells' minus: cells put
  in backwards leave it off and the board unpowered (it conducts both ways when they are right, so
  charging goes through it too). One cell reversed against the other is what the **per-cell fuses**
  are for: each holder's + reaches the pack through its own 2 A resettable fuse (Littelfuse
  1812L200/16GR: 16 V, 100 A interrupting), so a cell put in backwards, or one much fuller than
  the other, trips both in milliseconds instead of shorting the two cells together (tens of
  amperes); take the cell out and they reset. Still put each cell's + at the end the silkscreen
  marks.
- **Protection:** DW01A + FS8205A in the pack's minus: over-charge 4.3 V, over-discharge 2.4 V,
  over-current about 3 A and short circuit, for the pack.
- **Charger with power path:** a TI BQ24075 from the USB-C's VBUS (5.1 kΩ CC pull-downs: any USB-C
  charger gives 5 V), in USB500 mode (at most 500 mA from the port), 800 mA fast charge (RISET
  1.13 kΩ), input limit by RILIM 1.18 kΩ, safety timers off (two cells charge longer than its
  longest timer; termination is by current), TS tied to 10 kΩ (no thermistor). Its output SYS runs
  the board from USB when one is plugged in and from the cells otherwise.
- **Rails:** SYS feeds the TLV75533 LDO (3.3 V for the MCU, memories and display) and the
  MAX98357A directly. Near empty (3.0–3.3 V cells) the LDO drops out and 3.3 V follows the cells
  down; the F411, the memories and the ST7789 run to 2.7 V.
- **On/off:** the slide switch on the left edge drives the LDO's enable (off: the 3.3 V rail is off
  and the amplifier is shut down by its SD_MODE pull-up; the charger still charges).

| State | Current (estimate) |
|---|---|
| STM32F411 at 100 MHz | ~25 mA |
| PSRAM + flash active | ~15 mA |
| ST7789 2.0" with backlight | ~40 mA |
| MAX98357A playing | 20–200 mA from SYS |
| **Typical** | **~110 mA at 3.7 V** |

Two 3000 mAh cells → **~50 h**. A full charge of two empty cells at 800 mA takes about 8 h.

## Charging

Plug any USB-C charger or computer into the USB-C on the top edge. The red LED (CHG) is on while the
cells charge and goes out when they are full; the green LED (USB) is on while USB power is present.
The board runs from USB while it charges, switched on or off. Insert the cells with + at the end the
back's silkscreen marks.

## Modules plugged in by hand

The assembly solders a 1x8 female socket; the module is bought separately and plugged in:

- **DS1: 2.0" 240 × 320 ST7789 IPS SPI module** (MSP2008-type, 8 pins: GND, VCC, SCL, SDA, RES, DC,
  CS, BLK), on the front.
- An 8 Ω speaker (1–3 W) on the JST PH 2-pin connector J5 at the right edge.

## Firmware: build and flash

- **Build:** in PCBKit, the Laboratory's **Build & run** builds both programs (the F411's for
  Cortex-M4F with hard float; the guest for RV32IMAC with the WAD); then export the firmware
  (`export.run { format: "firmware" }`): `U1.bin` for the STM32F411 and `U3.bin` for the W25Q128.
- **The STM32F411, on arrival:** switch the board on, plug its USB-C into a computer, hold BOOT and
  press and release RESET (then release BOOT): the F411's ROM boot loader enumerates as "STM32
  BOOTLOADER" (USB DFU, 0483:df11). Then `dfu-util -a 0 -s 0x08000000:leave -D U1.bin` (or
  STM32CubeProgrammer). The ROM's DFU needs the 25 MHz HSE, which is fitted. Or over SWD: an
  ST-LINK on J1 (VCC, SWDIO, SWCLK, NRST, GND), `st-flash write U1.bin 0x8000000`.
- **The W25Q128 (the guest):** hold MENU while switching on: the firmware lets go of the memory bus
  and waits, so a USB SPI programmer (CH341A) with a SOIC-8 clip on the W25Q128 writes it in
  place: `flashrom -p ch341a_spi -w U3.bin`. Switch off and on: Doom boots.

## Bill of materials

Rough cost at 10 pieces (estimates, JLCPCB prices): STM32F411CEU6 $5.30 · APS6404L $4.00 · W25Q128
$2.60 · 25 MHz crystal $0.10 · ST7789 2.0" module $4.00 · MAX98357A $1.00 · BQ24075 $1.10 · DW01A +
FS8205A + AO3401A $0.25 · TLV75533 $0.15 · two Keystone 1042 $9.80 · USB-C $0.20 · buttons $2.50 ·
passives $1.00 · 4-layer PCB $3.50 → **about $35** without the cells and assembly fees.

<!-- BOM -->
The assembly BOM as `pcbkit export --format fab` writes it (JLCPCB assembly: LCSC codes; the modules' lines are their sockets):

| Qty | Refs | Part | LCSC | Footprint |
|---|---|---|---|---|
| 2 | BT1, BT2 | 1042 | C5249310 | BatteryHolder_Keystone_1042_1x18650 |
| 2 | C1, C2 | 15pF | C1548 | C_0402_1005Metric |
| 9 | C3, C4, C5, C8, C11, C13, C14, C16, C19 | 100nF | C1525 | C_0402_1005Metric |
| 4 | C6, C7, cBat, cSys | 4.7uF | C1779 | C_0805_2012Metric |
| 2 | C10, C12 | 1uF | C52923 | C_0402_1005Metric |
| 1 | C15 | 10uF | C15850 | C_0805_2012Metric |
| 3 | C20, C21, cIn | 1uF | C15849 | C_0603_1608Metric |
| 1 | D1 | tvs 5V | C502527 | D_SOD-323 |
| 1 | DS1 | MSP2008 2.0in 240x320 IPS SPI module (ST7789) | C2905417 | TFT_2.0in_ST7789_Socket_1x08_P2.54mm |
| 2 | F1, F2 | PTC 2000mA | C18198340 | Fuse_1812_4532Metric |
| 1 | J1 | PinHeader_1x05_P2.54mm_Vertical | C492404 | PinHeader_1x05_P2.54mm_Vertical |
| 1 | J2 | USB4105-GF-A | C165948 | USB_C_Receptacle_USB2.0_16P |
| 1 | J5 | S2B-PH-K-S(LF)(SN) | C173752 | JST_PH_S2B-PH-K_1x02_P2.00mm_Horizontal |
| 1 | Q1 | AO3401A | C15127 | SOT-23 |
| 1 | Q2 | FS8205A | C5148694 | TSSOP-8_4.4x2.93mm_P0.65mm |
| 7 | R1, R3, R4, R5, R6, R7, rTs | 10kohm | C25744 | R_0402_1005Metric |
| 2 | R2, R11 | 100kohm | C25741 | R_0402_1005Metric |
| 1 | R8 | 634kohm | C270588 | R_0402_1005Metric |
| 2 | R9, R10 | 5.1kohm | C25905 | R_0402_1005Metric |
| 1 | R14 | 100ohm | C25076 | R_0402_1005Metric |
| 1 | R15 | 1kohm | C11702 | R_0402_1005Metric |
| 8 | SW1, SW2, SW3, SW4, SW5, SW6, SW7, SW8 | PTS645SM43SMTR92 LFS | C221880 | SW_Tactile_SPST_6x6mm_SMD |
| 1 | SW9 | MSK12C02 | C431540 | SW_Slide_SPDT_Shouhan_MSK12C02 |
| 2 | SW10, SW11 | TS-1187A-B-A-B | C318884 | SW_Tactile_SPST_5.1x5.1mm_SMD |
| 1 | U1 | STM32F411CEU6 | C60420 | QFN-48-1EP_7x7mm_P0.5mm_EP5.6x5.6mm |
| 1 | U2 | APS6404L-3SQR-SN | C5333729 | SOIC-8_3.9x4.9mm_P1.27mm |
| 1 | U3 | W25Q128JVSIQ | C97521 | SOIC-8_5.23x5.28mm_P1.27mm |
| 1 | U4 | TLV75533PDBVR | C404027 | SOT-23-5 |
| 1 | U5 | MAX98357AETE+T | C910544 | QFN-16-1EP_3x3mm_P0.5mm_EP1.1x1.1mm |
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
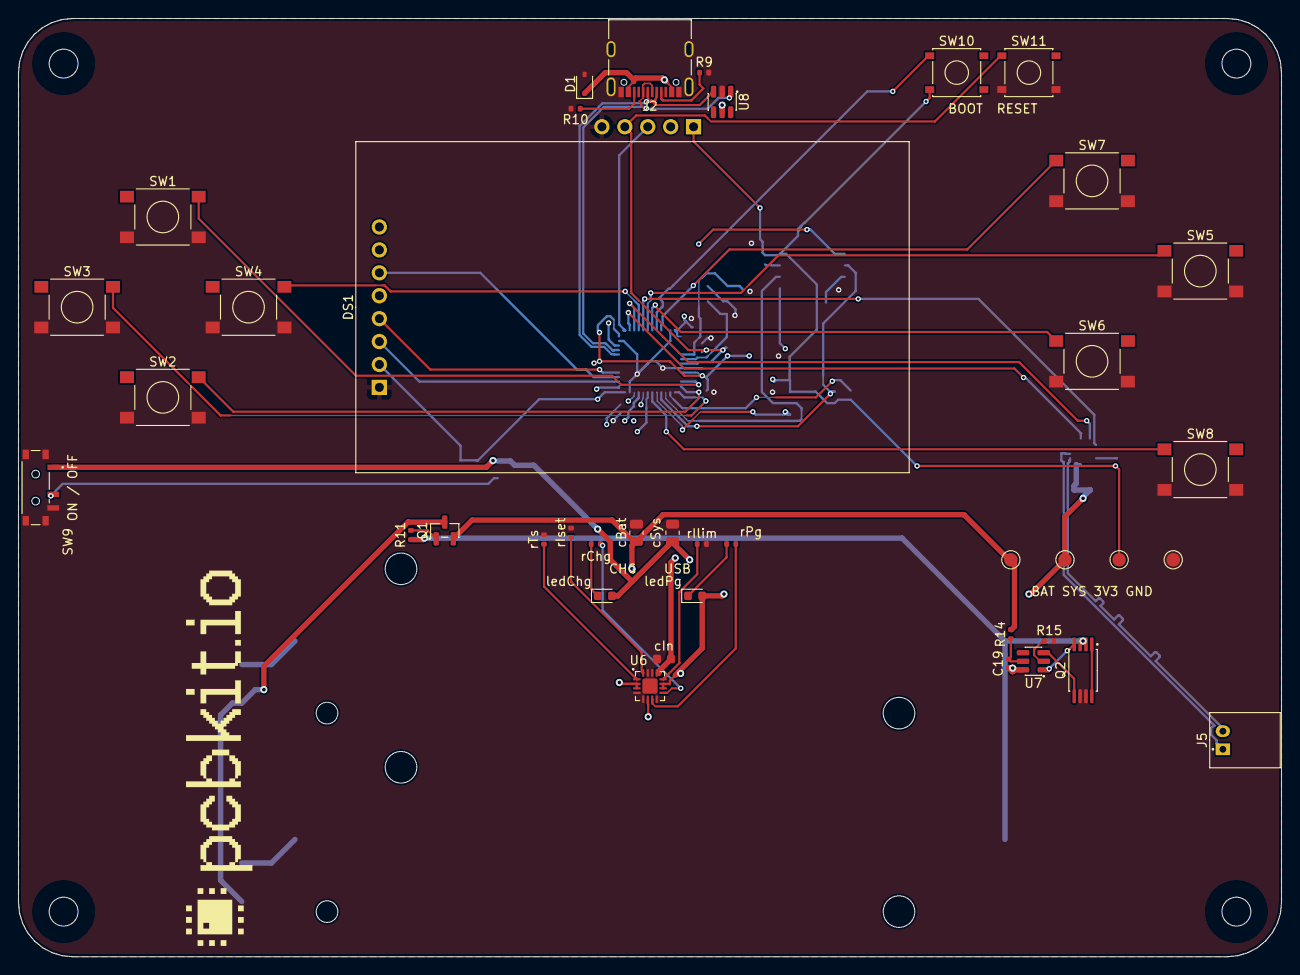
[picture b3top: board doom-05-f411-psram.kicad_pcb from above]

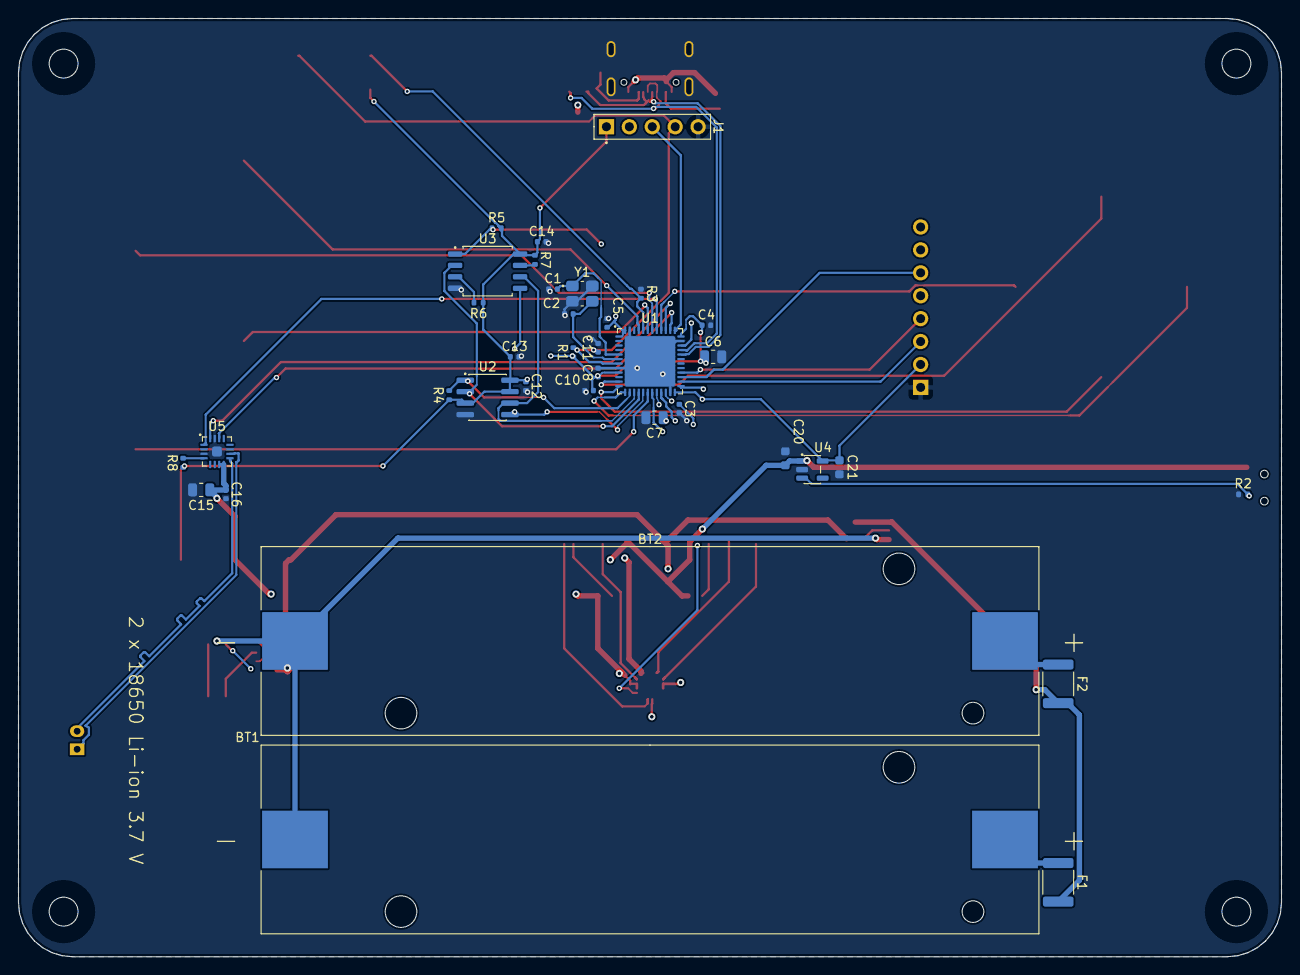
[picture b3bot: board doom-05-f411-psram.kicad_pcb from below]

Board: 4 copper layers, 140.0 x 104.0 mm, 81 parts (36 on the bottom side), 61 nets.

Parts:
BT1, BT2: 1042; BatteryHolder_Keystone_1042_1x18650
C1, C2: 15pF; C_0402_1005Metric
C3, C4, C5, C8, C11, C13, C14, C16, C19: 100nF; C_0402_1005Metric
C6, C7: 4.7uF; C_0805_2012Metric
C10, C12: 1uF; C_0402_1005Metric
C15: 10uF; C_0805_2012Metric
C20, C21: 1uF; C_0603_1608Metric
D1: tvs 5V; D_SOD-323
DS1: MSP2008 2.0in 240x320 IPS SPI module (ST7789); TFT_2.0in_ST7789_Socket_1x08_P2.54mm
F1, F2: PTC 2000mA; Fuse_1812_4532Metric
H1, H2, H3, H4: MountingHole_3.2mm_M3
J1: PinHeader_1x05_P2.54mm_Vertical
J2: USB4105-GF-A; USB_C_Receptacle_USB2.0_16P
J5: S2B-PH-K-S(LF)(SN); JST_PH_S2B-PH-K_1x02_P2.00mm_Horizontal
Q1: AO3401A; SOT-23
Q2: FS8205A; TSSOP-8_4.4x2.93mm_P0.65mm
R1, R3, R4, R5, R6, R7: 10kohm; R_0402_1005Metric
R2, R11: 100kohm; R_0402_1005Metric
R8: 634kohm; R_0402_1005Metric
R9, R10: 5.1kohm; R_0402_1005Metric
R14: 100ohm; R_0402_1005Metric
R15: 1kohm; R_0402_1005Metric
SW1, SW2, SW3, SW4, SW5, SW6, SW7, SW8: PTS645SM43SMTR92 LFS; SW_Tactile_SPST_6x6mm_SMD
SW9: MSK12C02; SW_Slide_SPDT_Shouhan_MSK12C02
SW10, SW11: TS-1187A-B-A-B; SW_Tactile_SPST_5.1x5.1mm_SMD
U1: STM32F411CEU6; QFN-48-1EP_7x7mm_P0.5mm_EP5.6x5.6mm
U2: APS6404L-3SQR-SN; SOIC-8_3.9x4.9mm_P1.27mm
U3: W25Q128JVSIQ; SOIC-8_5.23x5.28mm_P1.27mm
U4: TLV75533PDBVR; SOT-23-5
U5: MAX98357AETE+T; QFN-16-1EP_3x3mm_P0.5mm_EP1.1x1.1mm
U6: BQ24075RGTR; QFN-16-1EP_3x3mm_P0.5mm_EP1.68x1.68mm
U7: DW01A; SOT-6_1.6x2.9mm_P0.95mm
U8: USBLC6-2SC6; SOT-23-6
Y1: 25MHz 10pF; Crystal_SMD_3225-4Pin
cBat: 4.7uF; C_0805_2012Metric
cIn: 1uF; C_0603_1608Metric
cSys: 4.7uF; C_0805_2012Metric
ledChg: red; LED_0603_1608Metric
ledPg: green; LED_0603_1608Metric
logo: Logo_PCBKit_pcbkit.io
rChg: 1.5kohm; R_0402_1005Metric
rIlim: 1.18kohm; R_0402_1005Metric
rIset: 1.13kohm; R_0402_1005Metric
rPg: 1.5kohm; R_0402_1005Metric
rTs: 10kohm; R_0402_1005Metric
tpBat: TestPoint_Round_D1.5mm
tpGnd: TestPoint_Round_D1.5mm
tpSys: TestPoint_Round_D1.5mm
tpV3: TestPoint_Round_D1.5mm

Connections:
BAT: Q1.2 (S), R14.2 (b), U6.2 (BAT), U6.3 (BAT), cBat.1 (a), tpBat.1
BAT_IN: F1.2 (b), F2.2 (b), Q1.3 (D)
BOOT0: R3.1 (a), SW10.1 (a), U1.44 (BOOT0)
CELL1_P: BT1.2 (C2), F1.1 (a)
CELL2_P: BT2.2 (C2), F2.1 (a)
CELL_N: BT1.1 (C1), BT2.1 (C1), C19.1 (a), Q2.2 (S1), Q2.3 (S1), R11.1 (a), U7.6 (GND)
CHG_LED: ledChg.1 (K), rChg.1 (a)
CHG_N: U6.9 (nCHG), rChg.2 (b)
DN: J2.A7 (DN), J2.B7 (DN), U1.32 (PA11), U8.3 (IO2)
DOWN: SW2.1 (a), U1.12 (PA2)
DP: J2.A6 (DP), J2.B6 (DP), U1.33 (PA12), U8.1 (IO1)
FIRE: SW5.1 (a), U1.42 (PB6)
GND: C1.2 (b), C2.2 (b), C3.2 (b), C4.2 (b), C5.2 (b), C6.2 (b), C7.2 (b), C8.2 (b), C10.2 (b), C11.2 (b), C12.2 (b), C13.2 (b), C14.2 (b), C15.2 (b), C16.2 (b), C20.2 (b), C21.2 (b), D1.2 (A), DS1.1 (GND), J1.5, J2.A1 (GND), J2.A12, J2.B1 (GND), J2.B12, J2.S1 (SHIELD), Q2.6 (S2), Q2.7 (S2), R2.2 (b), R3.2 (b), R9.2 (b), R10.2 (b), R15.2 (b), SW1.2 (b), SW2.2 (b), SW3.2 (b), SW4.2 (b), SW5.2 (b), SW6.2 (b), SW7.2 (b), SW8.2 (b), SW9.3 (B), SW9.4 (SHELL), SW11.2 (b), U1.8 (VSSA), U1.23 (VSS), U1.35 (VSS), U1.47 (VSS), U1.49 (VSS), U2.4 (VSS), U3.4 (GND), U4.2 (GND), U5.3 (GND), U5.11 (GND), U5.15 (GND), U5.17 (EP), U6.4 (nCE), U6.5 (EN2), U6.8 (VSS), U6.14 (TMR), U6.15 (SYSOFF), U6.17 (VSS), U8.2 (GND), Y1.2 (GND), Y1.4 (GND), cBat.2 (b), cIn.2 (b), cSys.2 (b), rIlim.2 (b), rIset.2 (b), rTs.2 (b), tpGnd.1
I2S_CK: U1.39 (PB3), U5.16 (BCLK)
I2S_SD: U1.41 (PB5), U5.1 (DIN)
I2S_WS: U1.38 (PA15), U5.14 (LRCLK)
ILIM: U6.12 (ILIM), rIlim.1 (a)
ISET: U6.16 (ISET), rIset.1 (a)
LCD_BL: DS1.8 (BLK), U1.21 (PB10)
LCD_CS: DS1.7 (CS), U1.25 (PB12)
LCD_DC: DS1.6 (DC), U1.27 (PB14)
LCD_MOSI: DS1.4 (SDA), U1.28 (PB15)
LCD_RST: DS1.5 (RES), U1.19 (PB1)
LCD_SCK: DS1.3 (SCL), U1.26 (PB13)
LDO_EN: R2.1 (a), SW9.2 (COM), U4.3 (EN)
LEFT: SW3.1 (a), U1.13 (PA3)
MEM_MISO: U1.16 (PA6), U2.2 (SIO1), U3.2 (DO)
MEM_MOSI: U1.17 (PA7), U2.5 (SIO0), U3.5 (DI)
MEM_SCK: U1.15 (PA5), U2.6 (SCLK), U3.6 (CLK)
MENU: SW8.1 (a), U1.18 (PB0)
NRST: C11.1 (a), J1.4, R1.2 (b), SW11.1 (a), U1.7 (NRST)
unnamed: C1.1 (a), U1.5 (PH0), Y1.1 (X1)
unnamed: C2.1 (a), U1.6 (PH1), Y1.3 (X2)
unnamed: C19.2 (b), R14.1 (a), U7.5 (VCC)
unnamed: Q2.4 (G1), U7.1 (OD)
unnamed: Q2.5 (G2), U7.3 (OC)
unnamed: R6.2 (b), U3.3 (nWP)
unnamed: R7.2 (b), U3.7 (nHOLD)
unnamed: R8.2 (b), U5.4 (SD_MODE)
unnamed: R15.1 (a), U7.2 (CS)
PG_LED: ledPg.1 (K), rPg.1 (a)
PG_N: U6.7 (nPGOOD), rPg.2 (b)
RAM_CS: R4.2 (b), U1.14 (PA4), U2.1 (CE)
RIGHT: SW4.1 (a), U1.40 (PB4)
ROM_CS: R5.1 (a), U1.20 (PB2), U3.1 (nCS)
SPK_N: J5.1 (C1), U5.10 (OUTN)
SPK_P: J5.2 (C2), U5.9 (OUTP)
STRAFE: SW7.1 (a), U1.45 (PB8)
SWCLK: J1.3, U1.37 (PA14)
SWDIO: J1.2, U1.34 (PA13)
SYS: C15.1 (a), C16.1 (a), C20.1 (a), SW9.1 (A), U4.1 (IN), U5.7 (VDD), U5.8 (VDD), U6.6 (EN1), U6.10 (OUT), U6.11 (OUT), cSys.1 (a), ledChg.2 (A), ledPg.2 (A), tpSys.1
TS: U6.1 (TS), rTs.1 (a)
U7Support/DRAIN: Q2.1 (D12), Q2.8 (D12)
UP: SW1.1 (a), U1.11 (PA1)
USE: SW6.1 (a), U1.43 (PB7)
V3: C3.1 (a), C4.1 (a), C5.1 (a), C6.1 (a), C8.1 (a), C10.1 (a), C12.1 (a), C13.1 (a), C14.1 (a), C21.1 (a), DS1.2 (VCC), J1.1, R1.1 (a), R4.1 (a), R5.2 (b), R6.1 (a), R7.1 (a), R8.1 (a), SW10.2 (b), U1.1 (VBAT), U1.9 (VDDA), U1.24 (VDD), U1.36 (VDD), U1.48 (VDD), U2.3 (SIO2), U2.7 (SIO3), U2.8 (VDD), U3.8 (VCC), U4.5 (OUT), tpV3.1
VBUS: D1.1 (K), J2.A4 (VBUS), J2.A9, J2.B4 (VBUS), J2.B9, U6.13 (IN), U8.5 (VBUS), cIn.1 (a)
VCAP: C7.1 (a), U1.22 (VCAP1)
reversed/gate: Q1.1 (G), R11.2 (b)
usb/power/cc1: J2.A5 (CC1), R9.1 (a)
usb/power/cc2: J2.B5 (CC2), R10.1 (a)
